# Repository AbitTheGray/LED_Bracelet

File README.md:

# LED Bracelet

Single-cell LED Bracelet controlled by ESP32-C3.

While the bracelet/collar can work in "standalone" mode, it is recommended to connect it to other device using [BLE](https://en.wikipedia.org/wiki/Bluetooth_Low_Energy).

**This board is untested.**

Designed to be manufactured by [JLCPCB](https://jlcpcb.com/) as 4layer PCB with both inner layers acting as GND (you can probably use just the outer layers).

Requires [Espressif's KiCad Libraries](https://github.com/espressif/kicad-libraries).

## Features

- 5V LED strip
  - Designed for `WS2812` LEDs (=digital signal)
- 5V LED filament (outline)
  - Most of those filaments are 3V so use two of them, 2.5V should be enough
  - Can use PWM for brightness control
- USB-C charging
  - 5V 1.5A max (5.1k resistors)
  - `TP4056` charger
    - Status LEDs
      - Red = Charging
      - Blue = Standby
    - 1S 1A charging (1 cell in series, unlimited in parallel)
  - 1.5A discharge (`DW01A`)
  - Voltage measurement
    - 3/4 of voltage
    - Max 4.4V (=don't connect to 5V / USB)
- ESP32-C3 controller
  - BLE controls
  - Mode button to cycle colors
  - BOOT jumper pads (instead of a button)

### Warnings

- There are no reverse-polarity protections
- There are no fuses, you are responsible for maximum current on 5V output(s)
  - 1.2A shared between LED Strip and LED Filament connectors
    - max 20 RGB LEDs as `20*3*20mA = 1.2A` (`3` as the current is for each LED of RGB)
- Highlighted traces on silkscreen show voltages to measure (for testing)
- Some components are not in component placement
  - Use any `1206` LEDs (recommended colors are on silkscreen)
  - Mode button may need an uncommon component
  - Any THT connectors (battery + pin headers)
- Some components may need rotation tweak for fabrication
  - All `U` and `Q` components may need a rotation change (align 1st pin with long line on silkscreen)
  - `L1` needs 90deg rotation

### Possible future features

- Gyro+accelerometer to measure hand movement (available through BLE)
- Dedicated BLE button (BOOT button?) + status LED

## TODO

- Implement logic for `BLUETOOTH_ON_NO_CLIENT_WAIT`
  - Wait X seconds after turning the BLE ON, then turn it OFF if no client connected in the meantime
- Turn bluetooth OFF on critical battery level (and prevent it from turning on)
  - Compile define to disable this behavior
  - Add "What happens on Battery Critical?" section to [FAQ](FAQ.md)
- Compile define to independently disable Deep Sleep

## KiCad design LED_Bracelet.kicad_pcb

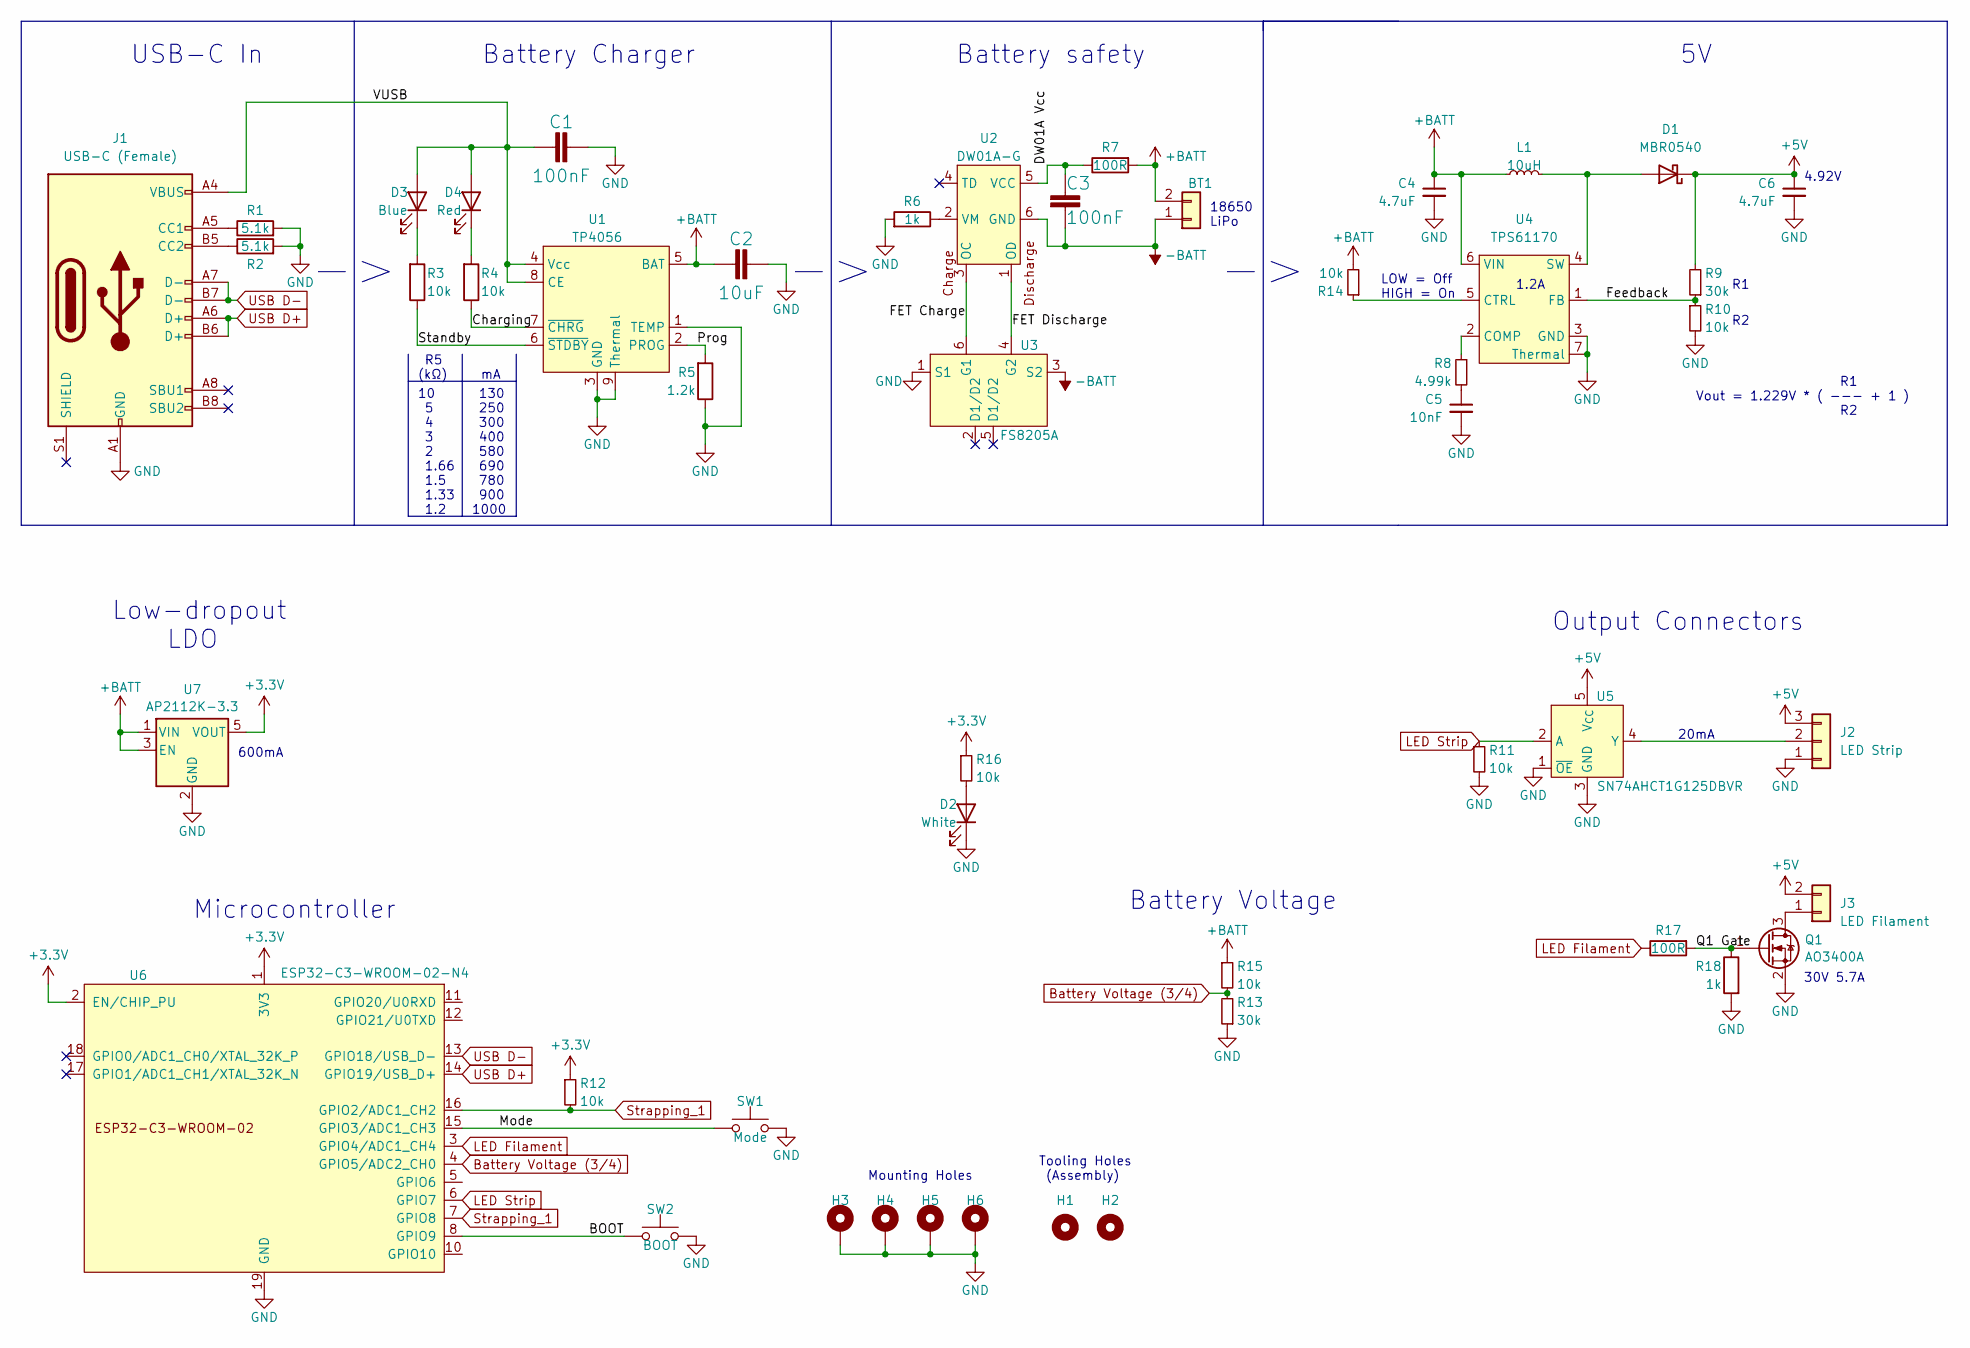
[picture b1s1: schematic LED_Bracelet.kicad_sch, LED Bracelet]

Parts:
BT1: Conn_01x02; JST_PH_B2B-PH-K_1x02_P2.00mm_Vertical
C1, C3: 100nF; C_0603_1608Metric; LCSC C14663
C2: 10uF; C_0603_1608Metric; LCSC C96446
C4, C6: 4.7uF; C_0603_1608Metric; LCSC C19666
C5: 10nF; C_0603_1608Metric; LCSC C57112
D1: MBR0540; D_SOD-123; LCSC C116159
D2: White; LED_1206_3216Metric
D3: Blue; LED_1206_3216Metric
D4: Red; LED_1206_3216Metric
H1, H2: MountingHole_Pad; JLCPCB ToolingHole
H3, H4, H5, H6: MountingHole_Pad; MountingHole_2.2mm_M2_ISO7380_Pad
J1: USB-C (Female); USB_C_Receptacle_GCT_USB4105-xx-A_16P_TopMnt_Horizontal; LCSC C2765186
J2: LED Strip; PinHeader_1x03_P2.54mm_Vertical
J3: LED Filament; PinHeader_1x02_P2.54mm_Vertical
L1: 10uH; Inductor 4x4; LCSC C497803
Q1: AO3400A; SOT-23; LCSC C20917
R1, R2: 5.1k; R_0603_1608Metric; LCSC C23186
R3, R4, R10, R11, R12, R14, R15, R16: 10k; R_0603_1608Metric; LCSC C25804
R5: 1.2k; R_0603_1608Metric; LCSC C22765
R6, R18: 1k; R_0603_1608Metric; LCSC C21190
R7, R17: 100R; R_0603_1608Metric; LCSC C22775
R8: 4.99k; R_0603_1608Metric; LCSC C2988946
R9, R13: 30k; R_0603_1608Metric; LCSC C22984
SW1: Mode; Panasonic_EVQPUL_EVQPUC
SW2: BOOT; SolderJumper-2_P1.3mm_Open_RoundedPad1.0x1.5mm
U1: TP4056; HSOP-8-1EP_3.9x4.9mm_P1.27mm_EP2.41x3.1mm_ThermalVias; LCSC C16581
U2: DW01A-G; SOT-23-6; LCSC C351410
U3: FS8205A; SOT-23-6; LCSC C908265
U4: TPS61170; DFN-6-1EP_2x2mm_P0.65mm_EP1.01x1.7mm; LCSC C15163
U5: SN74AHCT1G125DBVR; SOT-23-5; LCSC C7484
U6: ESP32-C3-WROOM-02-N4; ESP32-C3-WROOM-02; LCSC C2934560
U7: AP2112K-3.3; SOT-23-5; LCSC C51118

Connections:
+3.3V: R12.1, R16.1, U6.1 (3V3), U6.2 (EN/CHIP_PU), U7.5 (VOUT)
+5V: C6.1, D1.1 (K), J2.3, J3.2, R9.2, U5.5 (V_{CC})
+BATT: BT1.2, C2.1, C4.1, L1.1, R7.2, R14.2, R15.1, U1.5 (BAT), U4.6 (VIN), U7.1 (VIN), U7.3 (EN)
-BATT: BT1.1, C3.2, U2.6 (GND), U3.3 (S2)
/BOOT: SW2.2, U6.8 (GPIO9)
/Charging: R4.1, U1.7 (~CHRG)
/DW01A Vcc: C3.1, R7.1, U2.5 (VCC)
/FET Charge: U2.3 (OC), U3.6 (G1)
/FET Discharge: U2.1 (OD), U3.4 (G2)
/Feedback: R9.1, R10.1, U4.1 (FB)
/Mode: SW1.2, U6.15 (GPIO3/ADC1_CH3)
/Prog: R5.2, U1.2 (PROG)
/Q1 Gate: Q1.1 (G), R17.2, R18.1
/Standby: R3.1, U1.6 (~STDBY)
/VUSB: C1.1, D3.2 (A), D4.2 (A), J1.A4 (VBUS), J1.A9 (VBUS), J1.B4 (VBUS), J1.B9 (VBUS), U1.4 (Vcc), U1.8 (CE)
Battery Voltage (3/4): R13.2, R15.2, U6.4 (GPIO5/ADC2_CH0)
GND: C1.2, C2.2, C4.2, C5.2, C6.2, D2.1 (K), H3.1, H4.1, H5.1, H6.1, J1.A1 (GND), J1.A12 (GND), J1.B1 (GND), J1.B12 (GND), J2.1, Q1.2 (S), R1.2, R2.2, R5.1, R6.2, R10.2, R11.2, R13.1, R18.2, SW1.1, SW2.1, U1.1 (TEMP), U1.3 (GND), U1.9 (Thermal), U3.1 (S1), U4.3 (GND), U4.7 (Thermal), U5.1 (~OE), U5.3 (GND), U6.9 (GND), U6.19 (GND), U7.2 (GND)
LED Filament: R17.1, U6.3 (GPIO4/ADC1_CH4)
LED Strip: R11.1, U5.2 (A), U6.6 (GPIO7)
unnamed: C5.1, R8.2
unnamed: D1.2 (A), L1.2, U4.4 (SW)
unnamed: D2.2 (A), R16.2
unnamed: D3.1 (K), R3.2
unnamed: D4.1 (K), R4.2
unnamed: J1.A5 (CC1), R1.1
unnamed: J1.B5 (CC2), R2.1
unnamed: J2.2, U5.4 (Y)
unnamed: J3.1, Q1.3 (D)
unnamed: R6.1, U2.2 (VM)
unnamed: R8.1, U4.2 (COMP)
unnamed: R14.1, U4.5 (CTRL)
Strapping_1: R12.2, U6.7 (GPIO8), U6.16 (GPIO2/ADC1_CH2)
USB D+: J1.A6 (D+), J1.B6 (D+), U6.14 (GPIO19/USB_D+)
USB D-: J1.A7 (D-), J1.B7 (D-), U6.13 (GPIO18/USB_D-)

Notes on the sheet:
20mA
130 250 300 400 580 690 780 900 1000
Microcontroller
18650 LiPo
USB-C In
R5 (kΩ)
Tooling Holes (Assembly)
Low-dropout LDO
600mA
10 5 4 3 2 1.66 1.5 1.33 1.2
Output Connectors
Battery Charger
R1 Vout = 1.229V * ( --- + 1 ) R2
1.2A
30V 5.7A
Battery safety
Battery Voltage
Mounting Holes
LOW = Off HIGH = On
4.92V

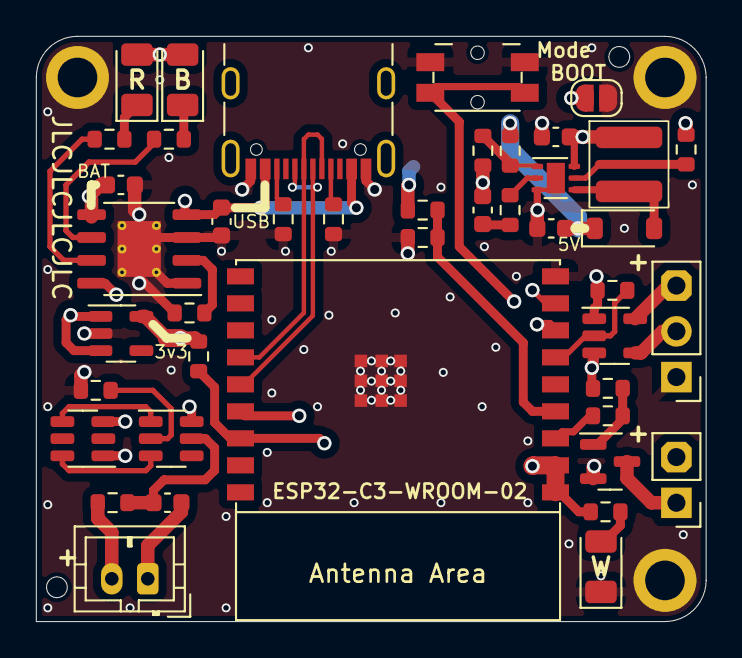
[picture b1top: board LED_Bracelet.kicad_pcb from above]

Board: 4 copper layers, 37.2 x 32.5 mm, 48 parts (0 on the bottom side), 34 nets.

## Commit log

2023-09-29 Complete schematic, position components on the PCB
2023-10-01 Tweaks to the PCB
2023-10-05 First software version + some PCB changes Separate BOOT and Mode buttons. LED Filament MOSFET (Q1) has pulldown resistor and is the correct channel. PlatformIO project + code. Frequently Asked Questi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
